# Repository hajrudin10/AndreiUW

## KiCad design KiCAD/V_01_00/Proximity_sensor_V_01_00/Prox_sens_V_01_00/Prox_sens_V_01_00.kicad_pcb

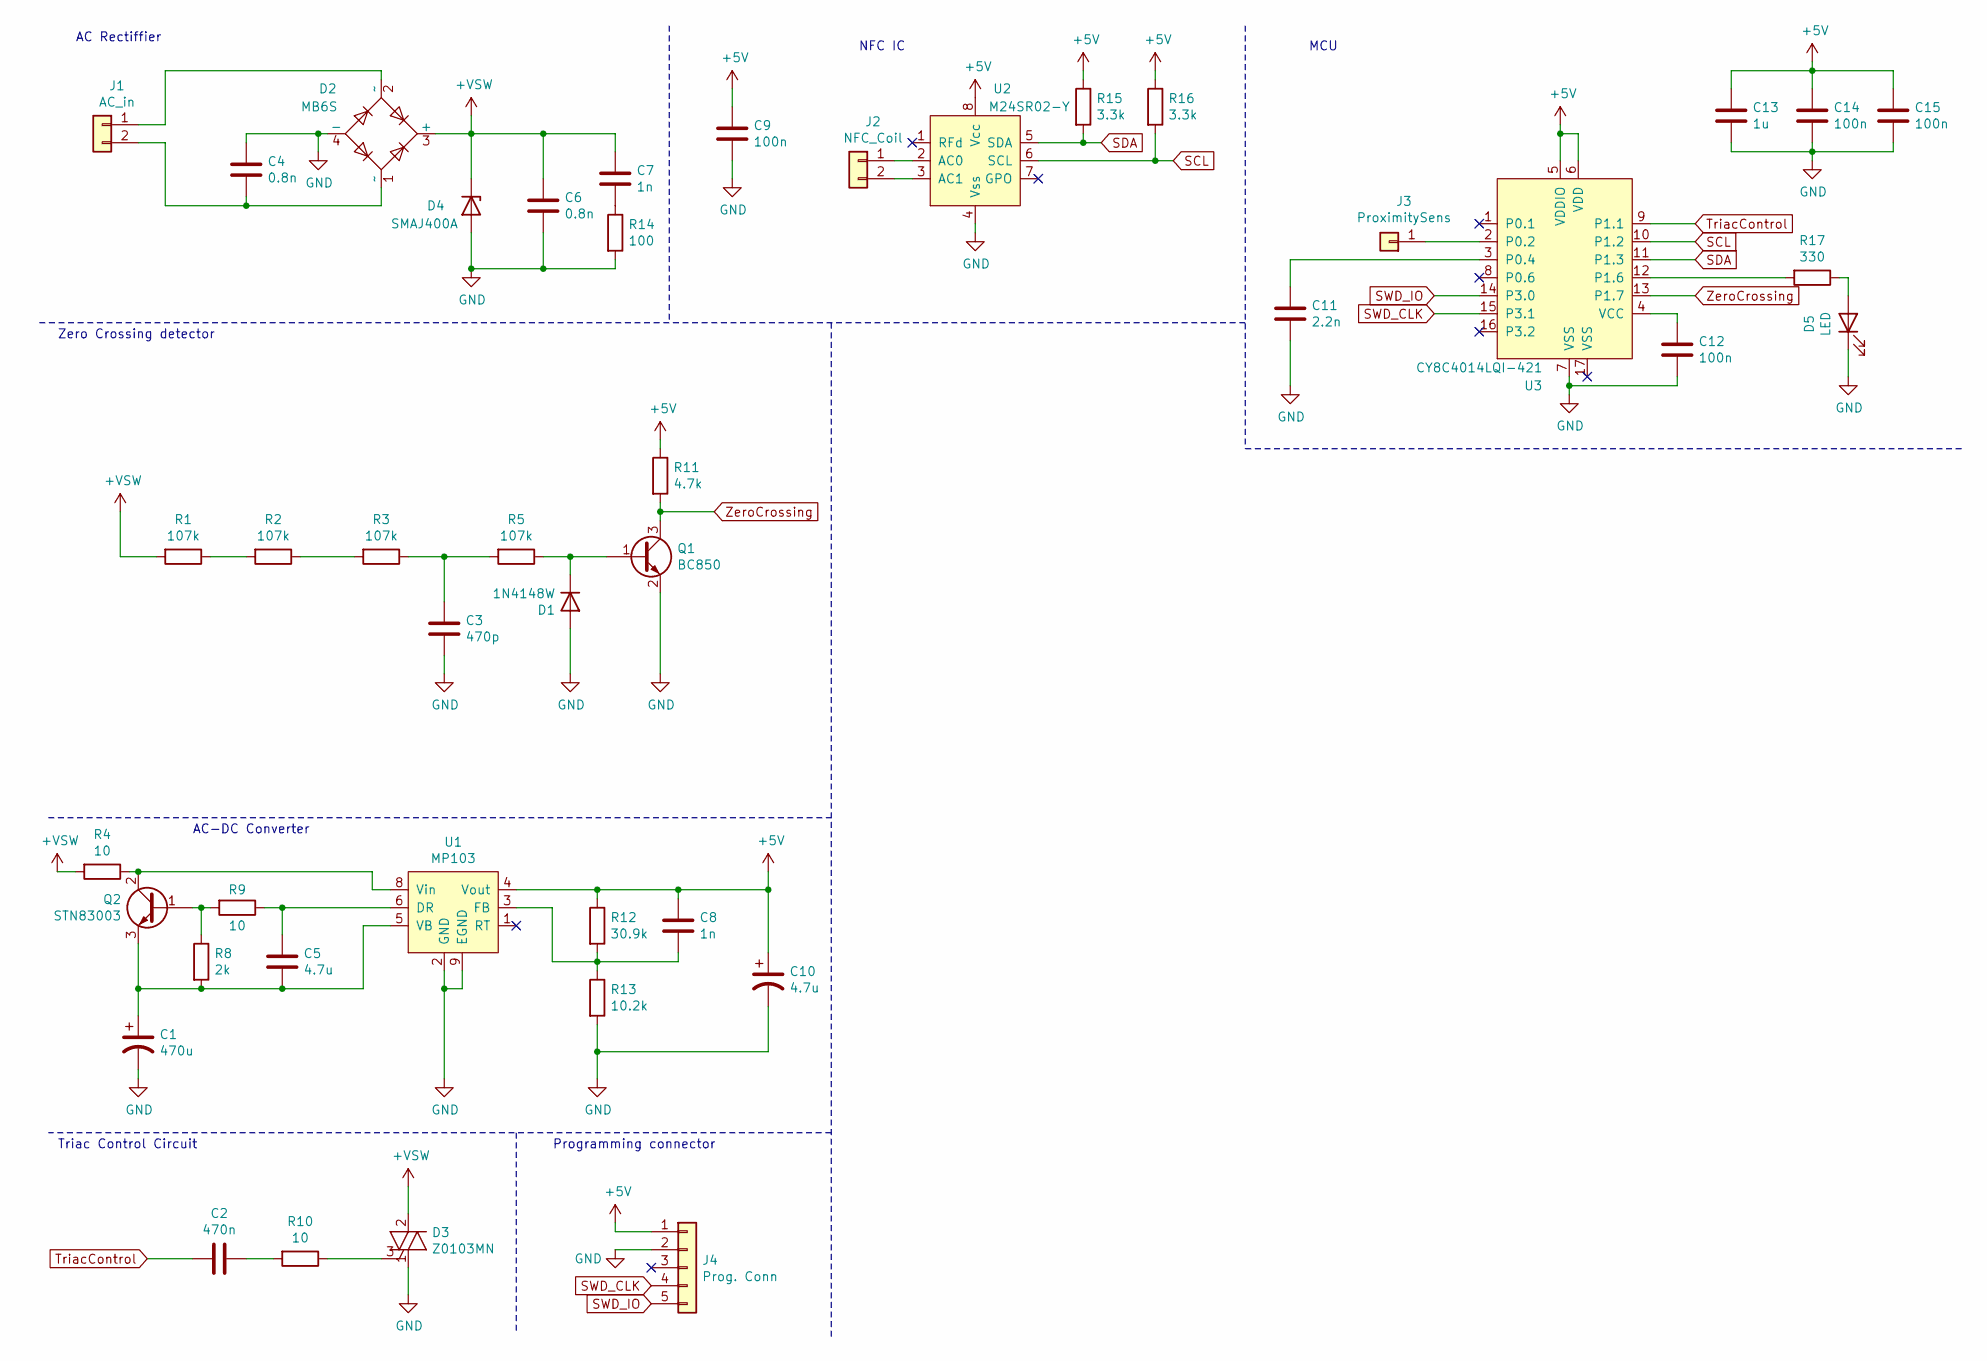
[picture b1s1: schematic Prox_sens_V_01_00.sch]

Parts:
C1: 470u; CP_Radial_D8.0mm_P3.50mm
C2: 470n; C_1206_3216Metric
C3: 470p; C_0805_2012Metric
C4, C6: 0.8n; C_1206_3216Metric
C5: 4.7u; C_0805_2012Metric
C7: 1n; C_1206_3216Metric
C8: 1n; C_0805_2012Metric
C9, C12, C14, C15: 100n; C_0805_2012Metric
C10: 4.7u; CP_EIA-3216-18_Kemet-A
C11: 2.2n; C_0805_2012Metric
C13: 1u; C_0805_2012Metric
D1: 1N4148W; D_0805_2012Metric
D2: MB6S; TO-269AA
D3: Z0103MN; SOT-223
D4: SMAJ400A; D_SMA
D5: LED; LED_0805_2012Metric
J1: AC_in; PinHeader_1x02_P5.08mm_Vertical
J2: NFC_Coil; PinHeader_1x02_P1.00mm_Vertical
J3: ProximitySens; Prox_sens
J4: Prog. Conn; PinHeader_1x05_P2.54mm_Vertical
Q1: BC850; SOT-23
Q2: STN83003; SOT-223-3_TabPin2
R1, R2, R3, R5: 107k; R_0805_2012Metric
R4, R10: 10; R_1206_3216Metric
R8: 2k; R_0805_2012Metric
R9: 10; R_0805_2012Metric
R11: 4.7k; R_0805_2012Metric
R12: 30.9k; R_0805_2012Metric
R13: 10.2k; R_0805_2012Metric
R14: 100; R_1206_3216Metric
R15, R16: 3.3k; R_0805_2012Metric
R17: 330; R_0805_2012Metric
U1: MP103; SOIC-8-1EP_3.9x4.9mm_P1.27mm_EP2.41x3.3mm
U2: M24SR02-Y; TSSOP-8_4.4x3mm_P0.65mm
U3: CY8C4014LQI-421; QFN-16-1EP_3x3mm_P0.5mm_EP1.75x1.75mm

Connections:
+5V: C8.1, C9.1, C10.1, C13.1, C14.1, C15.1, J4.1, R11.1, R12.1, R15.1, R16.1, U1.4 (Vout), U2.8 (Vcc), U3.5 (VDDIO), U3.6 (VDD)
+VSW: C6.1, C7.1, D2.3 (+), D3.2 (A2), D3.4 (A4), D4.1 (K), R1.2, R4.2
GND: C1.2, C3.2, C4.1, C6.2, C9.2, C10.2, C11.2, C12.2, C13.2, C14.2, C15.2, D1.2 (A), D2.4 (-), D3.1 (A1), D4.2 (A), D5.1 (K), J4.2, Q1.2 (E), R13.2, R14.2, U1.2 (GND), U1.9 (EGND), U2.4 (Vss), U3.7 (VSS)
unnamed: C1.1, C5.2, Q2.3 (E), R8.2, U1.5 (VB)
unnamed: C2.1, R10.2
unnamed: C3.1, R3.1, R5.2
unnamed: C4.2, D2.1 (~~), J1.2
unnamed: C5.1, R9.1, U1.6 (DR)
unnamed: C7.2, R14.1
unnamed: C8.2, R12.2, R13.1, U1.3 (FB)
unnamed: C11.1, U3.3 (P0.4)
unnamed: C12.1, U3.4 (VCC)
unnamed: D1.1 (K), Q1.1 (B), R5.1
unnamed: D2.2 (~~), J1.1
unnamed: D3.3 (G), R10.1
unnamed: D5.2 (A), R17.1
unnamed: J2.1, U2.2 (AC0)
unnamed: J2.2, U2.3 (AC1)
unnamed: J3.1, U3.2 (P0.2)
unnamed: Q2.1 (B), R8.1, R9.2
unnamed: Q2.2 (C), R4.1, U1.8 (Vin)
unnamed: R1.1, R2.2
unnamed: R2.1, R3.2
unnamed: R17.2, U3.12 (P1.6)
SCL: R16.2, U2.6 (SCL), U3.10 (P1.2)
SDA: R15.2, U2.5 (SDA), U3.11 (P1.3)
SWD_CLK: J4.4, U3.15 (P3.1)
SWD_IO: J4.5, U3.14 (P3.0)
TriacControl: C2.2, U3.9 (P1.1)
ZeroCrossing: Q1.3 (C), R11.2, U3.13 (P1.7)

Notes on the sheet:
AC Rectiffier
Zero Crossing detector
Triac Control Circuit
AC-DC Converter
NFC IC
MCU
Programming connector

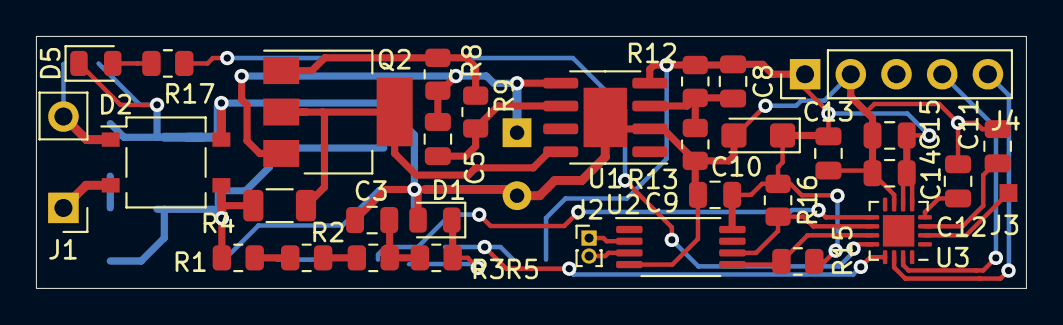
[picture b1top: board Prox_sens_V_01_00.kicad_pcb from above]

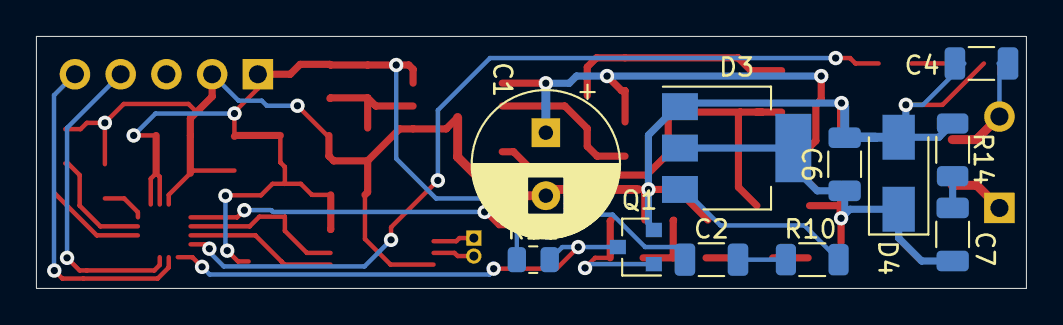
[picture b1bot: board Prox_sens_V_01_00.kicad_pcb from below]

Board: 2 copper layers, 55.0 x 14.0 mm, 44 parts (11 on the bottom side), 30 nets.

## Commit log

2021-07-18 schem
2021-08-02 change
